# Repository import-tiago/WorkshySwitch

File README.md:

# WorkshySwitch

WorkshySwitch is an IoT device for wireless control of lamps without harming the use of the physical switch.

## Features
##### Controller Device / [SoC CC2541 with 8051 MCU and Embedded Bluetooth 4.0](http://www.ti.com/lit/ds/symlink/cc2541.pdf)

##### Wireless Technology / [Embedded Meandered Inverted F Antenna (MIFA) with 50 ohm at 2.45 GHz](https://github.com/import-tiago/WorkshySwitch/blob/master/Hardware/3.%20Datasheets/MCU/CC25XX%20-%20Small%20Size%202.4%20GHz%20PCB%20antenna.pdf)

##### Low Power Requirements / Does not apply in this project

##### Hardware Project / [Autodesk EAGLE](https://www.autodesk.com/products/eagle/free-download)

##### Firmware Project / [IAR Embedded Workbench](https://www.iar.com/iar-embedded-workbench/)

##### 3D Model Project / [Autodesk Fusion 360](https://www.autodesk.com/products/fusion-360/overview#banner)

## PCB Details

## How to Connect

## Schematic

### Contributing
0. Give this project a :star:
1. Create an issue and describe your idea.
2. [Fork it](https://github.com/import-tiago/WorkshySwitch/fork).
3. Create your feature branch (`git checkout -b my-new-feature`).
4. Commit your changes (`git commit -a -m "Added feature title"`).
5. Publish the branch (`git push origin my-new-feature`).
6. Create a new pull request.
7. Done! :heavy_check_mark:

### License Information
<br /><span xmlns:dct="http://purl.org/dc/terms/" property="dct:title">WorkshySwitch</span> by <a xmlns:cc="http://creativecommons.org/ns#" href="https://github.com/import-tiago" property="cc:attributionName" rel="cc:attributionURL">Tiago Silva</a> is licensed under a <a rel="license" href="http://creativecommons.org/licenses/by-sa/4.0/">Creative Commons Attribution-ShareAlike 4.0 International License</a>.<br />Permissions beyond the scope of this license may be available at <a xmlns:cc="http://creativecommons.org/ns#" href="https://twitter.com/import_tiago" rel="cc:morePermissions">tiagodepaulasilva@gmail.com</a>.

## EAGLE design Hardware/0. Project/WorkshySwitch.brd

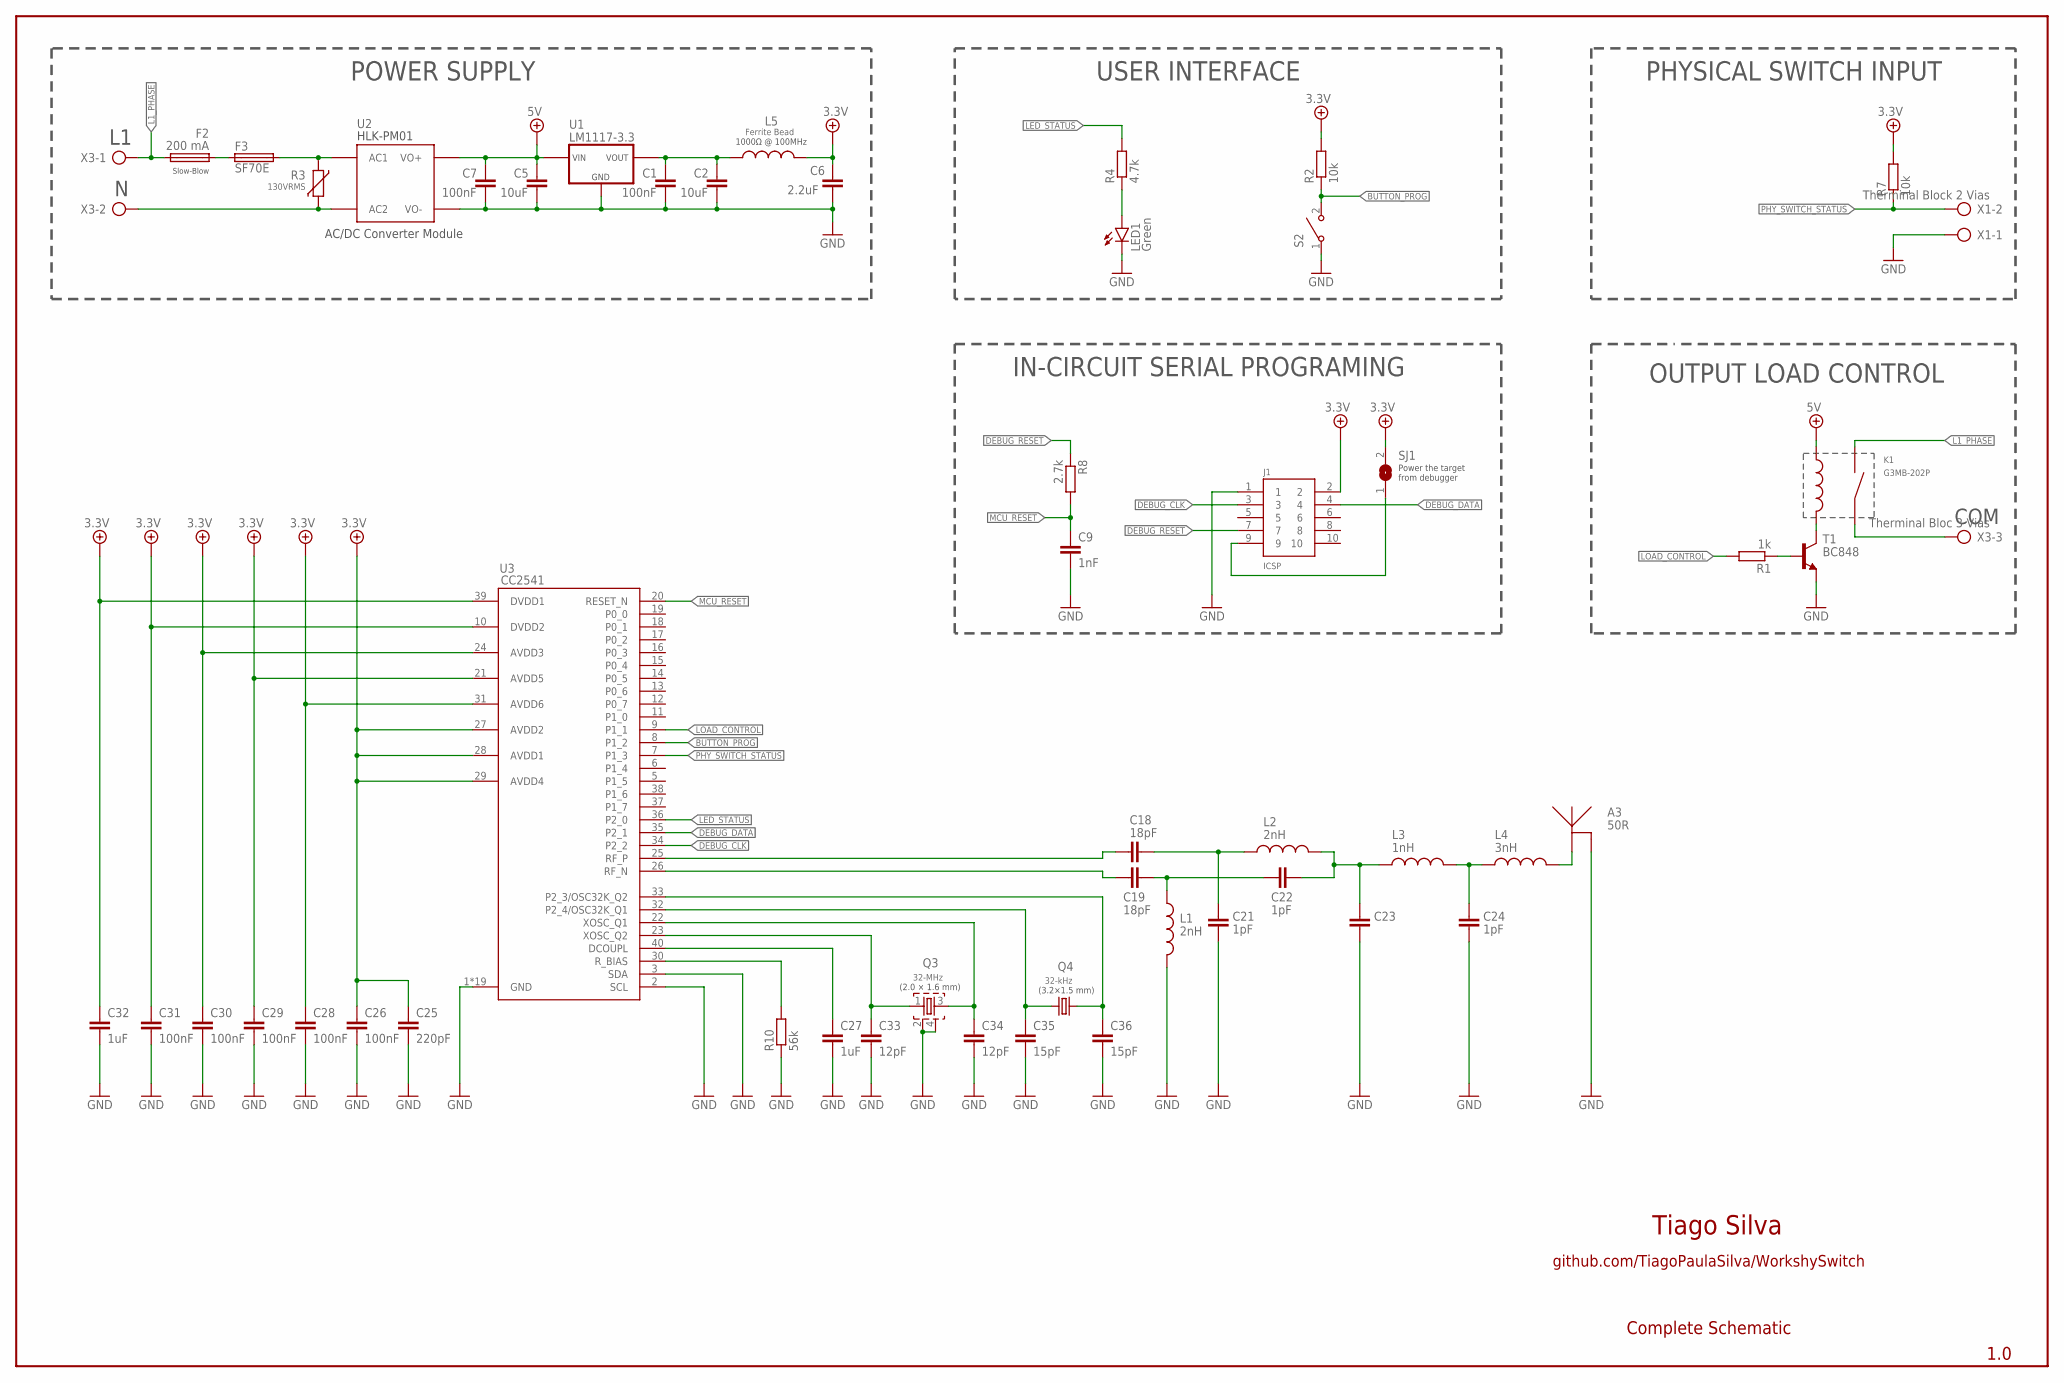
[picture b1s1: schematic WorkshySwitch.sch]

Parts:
A3: 50R; MIFA
C1, C7: 100nF; C0603
C2, C5: 10uF; C0603
C6: 2.2uF; C0402
C9: 1nF; C0402
C18, C19: 18pF; C0402
C21, C22, C24: 1pF; C0402
C23: C0402
C25: 220pF; C0402
C26, C28, C29, C30, C31: 100nF; C0402
C27, C32: 1uF; C0402
C33, C34: 12pF; C0402
C35, C36: 15pF; C0402
F2: 200 mA; QPL
F3: SF70E; LITTLEFUSE
J1: ICSP; SHF-105-01-X-D-SM
K1: G3MB-202P; RELAY_G3MB202PDC12
L1, L2: 2nH; C0402
L3: 1nH; C0402
L4: 3nH; C0402
L5: Ferrite Bead; C0402
LED1: Green; CHIP-LED0805
Q3: 32-MHz; FA-128
Q4: 32-kHz; 3.2X1.5
R1: 1k; C0402
R2, R7: 10k; C0402
R3: 130VRMS; S05K11
R4: 4.7k; C0402
R8: 2.7k; C0402
R10: 56k; C0402
S2: 434121050816
SJ1: Jumper; SJ
T1: BC848; SOT23
U1: LM1117-3.3; SOT223
U2: HLK-PM01
U3: CC2541; QFN50P600X600X100-41N
X1: Therminal Block 2 Vias; AK500/2
X3: Therminal Bloc 3 Vias; AK500/3

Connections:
3.3: C1.1, C2.1, L5.2, U1.2 (VOUT), U1.4 (VOUT)
3.3V: C6.1, C25.1, C26.1, C28.1, C29.1, C30.1, C31.1, C32.1, J1.2, L5.1, R2.2, R7.2, SJ1.2, U3.10 (DVDD2), U3.21 (AVDD5), U3.24 (AVDD3), U3.27 (AVDD2), U3.28 (AVDD1), U3.29 (AVDD4), U3.31 (AVDD6), U3.39 (DVDD1)
5V: C5.1, C7.1, K1.3 (+), U1.3 (VIN), U2.P$4 (VO+)
BUTTON_PROG: R2.1, S2.2, U3.8 (P1_2)
DEBUG_CLK: J1.3, U3.34 (P2_2)
DEBUG_DATA: J1.4, U3.35 (P2_1)
DEBUG_RESET: J1.7, R8.1
GND: A3.GND, C1.2, C2.2, C5.2, C6.2, C7.2, C9.2, C21.2, C23.1, C24.2, C25.2, C26.2, C27.2, C28.2, C29.2, C30.2, C31.2, C32.2, C33.2, C34.2, C35.2, C36.2, J1.1, L1.2, LED1.C, Q3.2, Q3.4, R10.1, S2.1, T1.2 (E), U1.1 (GND), U2.P$3 (VO-), U3.1 (GND), U3.2 (SCL), U3.3 (SDA), U3.4 (GND), U3.41 (GND), U3.42 (GND), U3.43 (GND), U3.44 (GND), U3.45 (GND), U3.46 (GND), U3.47 (GND), U3.48 (GND), U3.49 (GND), U3.50 (GND), U3.51 (GND), U3.52 (GND), U3.53 (GND), U3.54 (GND), U3.55 (GND), U3.56 (GND), U3.57 (GND), X1.1
L1_PHASE: F2.2, K1.1 (L1), X3.1
LED_STATUS: R4.2, U3.36 (P2_0)
LOAD_CONTROL: R1.2, U3.9 (P1_1)
MCU_RESET: C9.1, R8.2, U3.20 (RESET_N)
unnamed: LED1.A, R4.1
unnamed: R3.2, U2.P$2 (AC2), X3.2
unnamed: F3.2, R3.1, U2.P$1 (AC1)
unnamed: K1.4 (-), T1.3 (C)
unnamed: R1.1, T1.1 (B)
unnamed: K1.2 (L2), X3.3
unnamed: F2.1, F3.1
unnamed: J1.9, SJ1.1
unnamed: C18.1, U3.25 (RF_P)
unnamed: C19.1, C22.2, L1.1
unnamed: C22.1, C23.2, L2.2, L3.1
unnamed: C19.2, U3.26 (RF_N)
unnamed: C18.2, C21.1, L2.1
unnamed: C24.1, L3.2, L4.1
unnamed: A3.FEED, L4.2
unnamed: C27.1, U3.40 (DCOUPL)
unnamed: R10.2, U3.30 (R_BIAS)
unnamed: C33.1, Q3.1, U3.23 (XOSC_Q2)
unnamed: C34.1, Q3.3, U3.22 (XOSC_Q1)
unnamed: C35.1, Q4.1, U3.32 (P2_4/OSC32K_Q1)
unnamed: C36.1, Q4.2, U3.33 (P2_3/OSC32K_Q2)
PHY_SWITCH_STATUS: R7.1, U3.7 (P1_3), X1.2

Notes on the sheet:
Tiago Silva
github.com/TiagoPaulaSilva/WorkshySwitch
1.0
Complete Schematic
AC/DC Converter Module
POWER SUPPLY
PHYSICAL SWITCH INPUT
OUTPUT LOAD CONTROL
COM
Slow-Blow
(3.2×1.5 mm)
(2.0 × 1.6 mm)
1000Ω @ 100MHz
Power the target from debugger
USER INTERFACE
IN-CIRCUIT SERIAL PROGRAMING

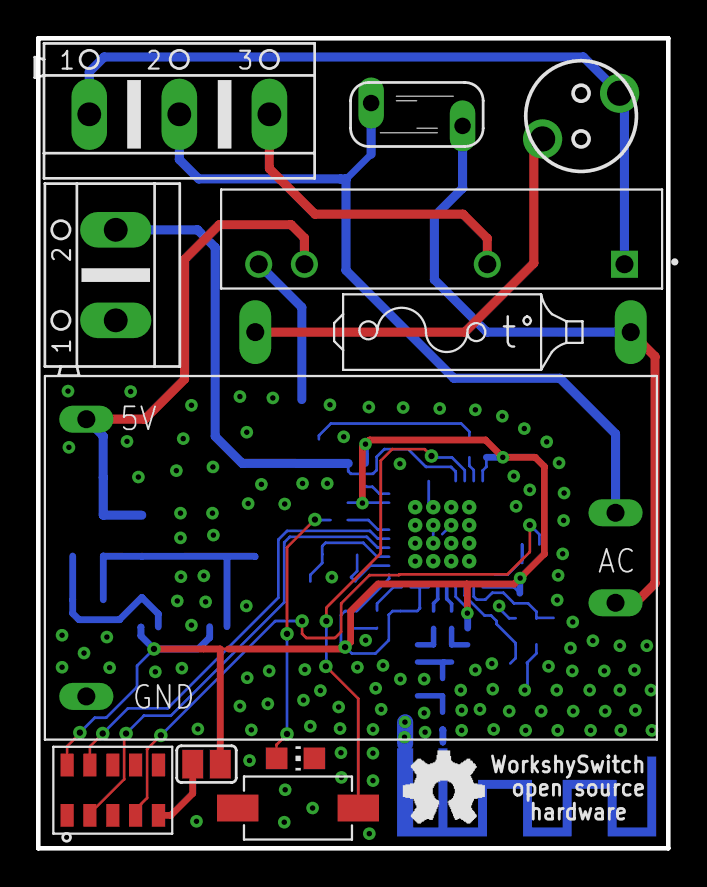
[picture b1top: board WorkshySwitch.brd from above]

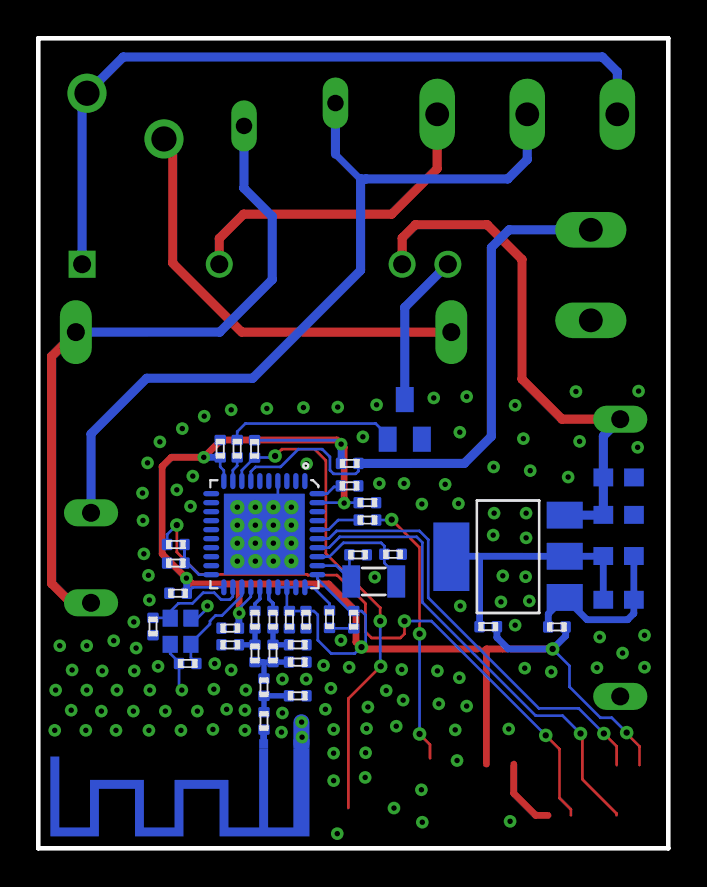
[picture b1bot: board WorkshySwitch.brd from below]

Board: 2 copper layers, 35.0 x 45.0 mm, 52 parts (41 on the bottom side), 34 nets.

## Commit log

2019-07-09 Temporary eagle files removed
2019-07-09 Readme updated
2019-07-10 Protect circuit added
2019-07-10 PCB layout under dev
2019-07-10 Flowchart added
2019-07-10 Eagle description file removed
2019-07-17 New hardware design approch
    - The previous approach would be too large.
    - Now, MCU and BLE module don't exists anymore.
    - A new MCU with embedded BLE was added: CC2541.
2019-07-17 Reduced number of PTR connectors
2019-07-20 PCB layout done
2019-07-20 Gerbers files generated
2019-07-20 3D PCB Model Generated
2019-07-20 Components values added
2019-07-20 MCU datasheets updated
2019-07-21 Gerber files updated
2019-07-22 Width of top polygon increased
2019-07-22 Minor improvement in the TOP layer
2019-07-22 .gitattributes file added
2019-07-22 .gitattributes file updated
2019-11-16 New images added
2023-07-21 usernames in URLs updated

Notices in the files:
parts and their libraries:
crystal-geyer_V1_0: Copyright: Geyer-Electronic
